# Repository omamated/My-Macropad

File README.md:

# My-Macropad
My 6 key macropad that also has a 0.91" OLED and a rotary encoder.

Some of my work in Kicad:

Some of my other work in Fusion 360

All of these softwares were realatively new to me except fusion 360 as I had some experience and the same with Python.

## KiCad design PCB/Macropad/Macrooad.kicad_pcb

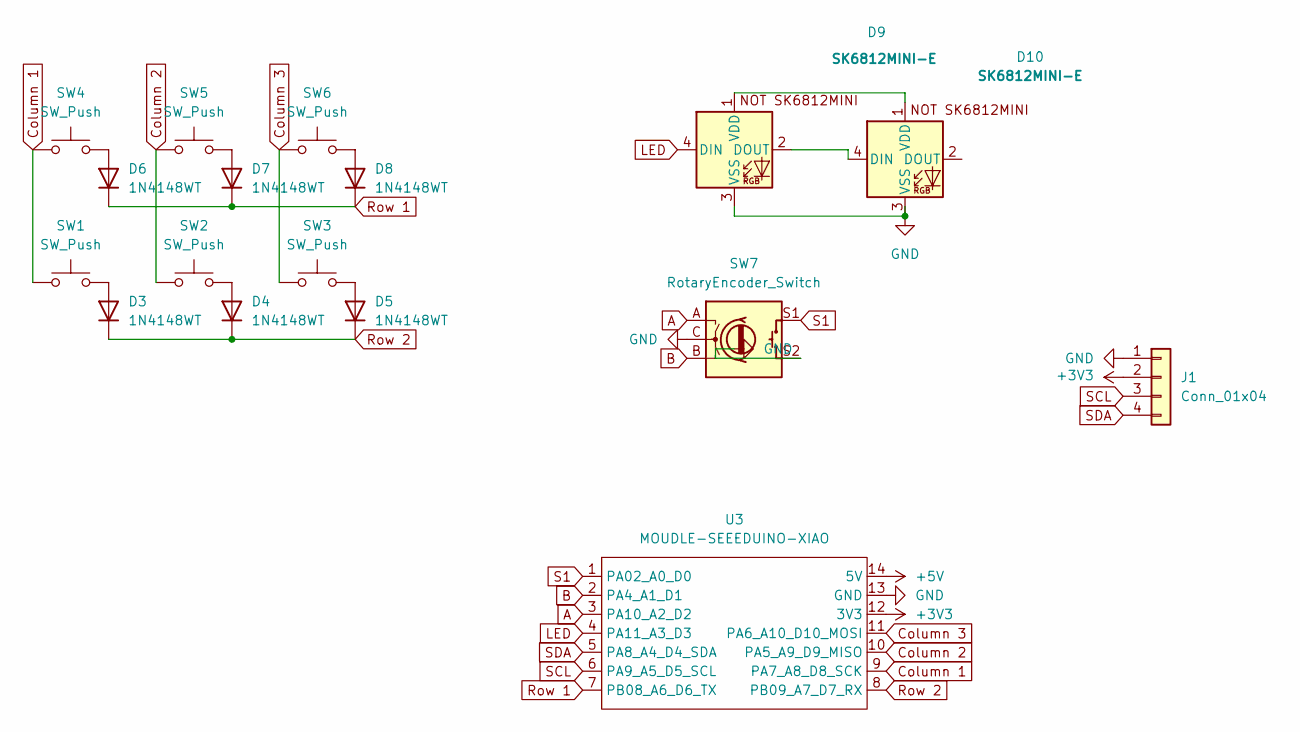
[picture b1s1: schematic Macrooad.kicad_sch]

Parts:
D3, D4, D5, D6, D7, D8: 1N4148WT; D_DO-35_SOD27_P2.54mm_Vertical_AnodeUp
D9, D10: SK6812MINI-E; SK6812MINI-E_fixed
J1: Conn_01x04; SSD1306-0.91-OLED-4pin-128x32 (2)
SW1, SW2, SW3, SW4, SW5, SW6: SW_Push; SW_Cherry_MX_1.00u_PCB
SW7: RotaryEncoder_Switch; RotaryEncoder_Alps_EC11E-Switch_Vertical_H20mm
U3: MOUDLE-SEEEDUINO-XIAO; XIAO-RP2040-DIP

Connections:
+3V3: J1.2, U3.12 (3V3)
+5V: U3.14 (5V)
A: SW7.A, U3.3 (PA10_A2_D2)
B: SW7.B, U3.2 (PA4_A1_D1)
Column 1: SW1.1, SW4.1, U3.9 (PA7_A8_D8_SCK)
Column 2: SW2.1, SW5.1, U3.10 (PA5_A9_D9_MISO)
Column 3: SW3.1, SW6.1, U3.11 (PA6_A10_D10_MOSI)
GND: D9.3 (VSS), D10.3 (VSS), J1.1, SW7.C, SW7.S2, U3.13 (GND)
LED: D9.4 (DIN), U3.4 (PA11_A3_D3)
unnamed: D3.2 (A), SW1.2
unnamed: D4.2 (A), SW2.2
unnamed: D5.2 (A), SW3.2
unnamed: D6.2 (A), SW4.2
unnamed: D7.2 (A), SW5.2
unnamed: D8.2 (A), SW6.2
unnamed: D9.2 (DOUT), D10.4 (DIN)
unnamed: D9.1 (VDD), D10.1 (VDD)
Row 1: D6.1 (K), D7.1 (K), D8.1 (K), U3.7 (PB08_A6_D6_TX)
Row 2: D3.1 (K), D4.1 (K), D5.1 (K), U3.8 (PB09_A7_D7_RX)
S1: SW7.S1, U3.1 (PA02_A0_D0)
SCL: J1.3, U3.6 (PA9_A5_D5_SCL)
SDA: J1.4, U3.5 (PA8_A4_D4_SDA)

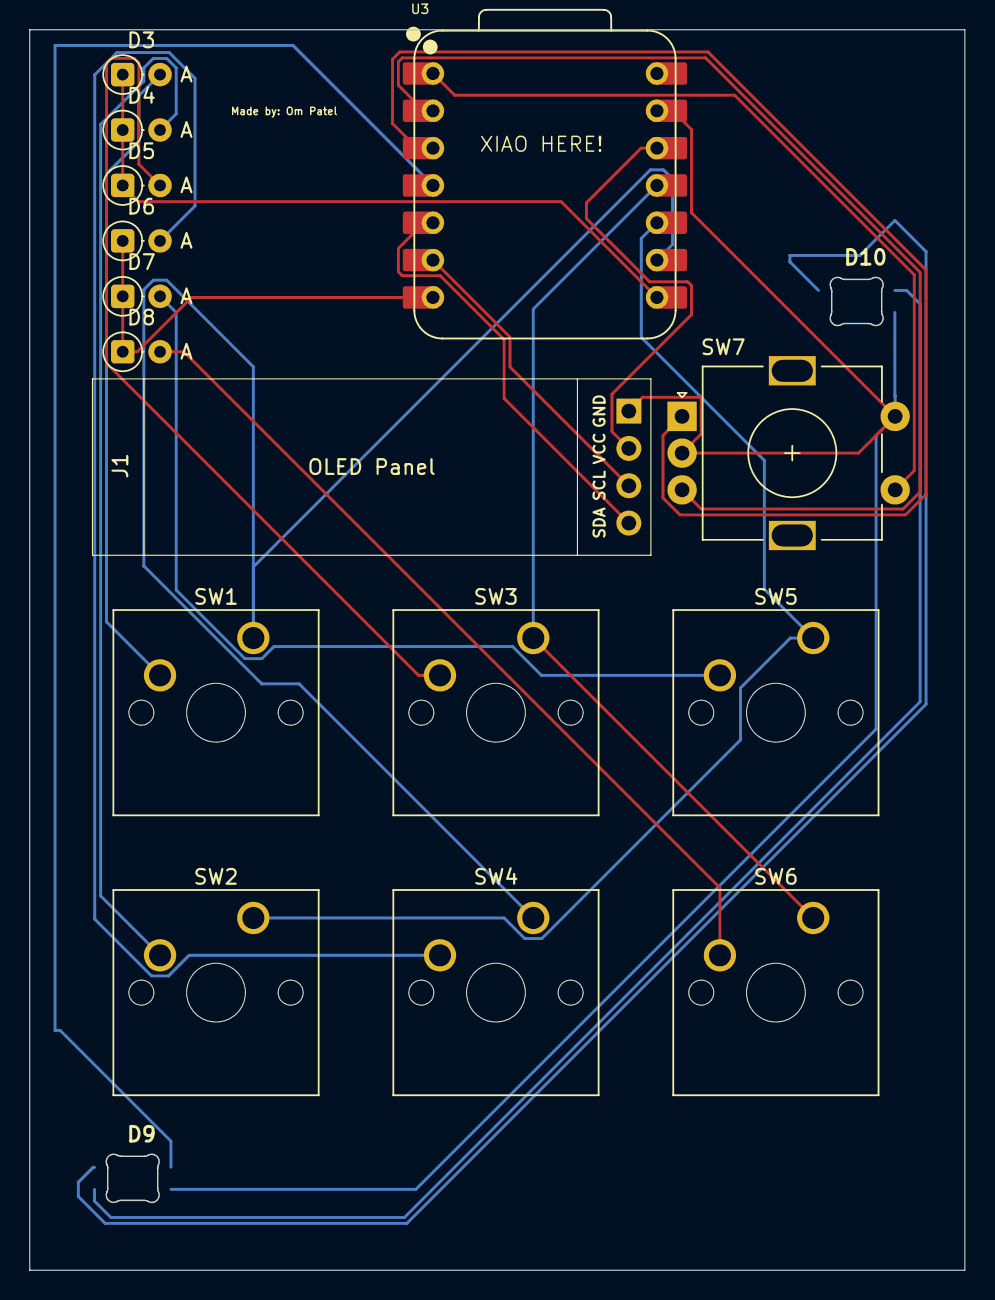
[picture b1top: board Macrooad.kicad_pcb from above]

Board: 2 copper layers, 63.6 x 84.4 mm, 17 parts (0 on the bottom side), 21 nets.

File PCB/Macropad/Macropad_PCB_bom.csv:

Designator,Footprint,Quantity,Value,LCSC Part #
"D10, D9",SK6812MINI-E_fixed,2,SK6812MINI-E,
"D3, D4, D5, D6, D7, D8",D_DO-35_SOD27_P2.54mm_Vertical_AnodeUp,6,1N4148WT,
J1,SSD1306-0.91-OLED-4pin-128x32 (2),1,Conn_01x04,
"SW1, SW2, SW3, SW4, SW5, SW6",SW_Cherry_MX_1.00u_PCB,6,SW_Push,
SW7,RotaryEncoder_Alps_EC11E-Switch_Vertical_H20mm,1,RotaryEncoder_Switch,
U3,XIAO-RP2040-DIP,1,MOUDLE-SEEEDUINO-XIAO,

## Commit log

2025-12-08 Uploading the CAD
2025-12-08 Create CAD
